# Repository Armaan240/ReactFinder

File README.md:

# ReactFinder

React Finder is Mememory Testing Game which works like , when you press the start button four led makes a Interesting Sequence and a order , the game is simple follow the exsact order of leds if you pressed correct button buzzer beeps and all are pressed correct Buzzer Beeps with A winning sound and New Level will start harder than the other , currently it have only 10 levels But All of them Are random so You can Still Enjoy if all of them is Played which difficult but Who knows , if only one sequence was pressed incorrectly buzzer beeps with a losing sound and thus you have to restart 

---
### Why i Made This?
i always Wnated to create A hardware based Game, so pathfinder hepled me and give me a motivation so that i could make a tick on my bucket list , also i thanks to meghana , she hepled me out in every doubt is asked i liked her patience and kindness which led to make React Finder 

### Some Key Features 

* 4 LEDs Turn on in a random Order 
* Press buttons to repeat the correct sequence with A buzzer beep
* Win = buzzer celebration sound + level up
* Lose = if you were un Successfull in Order ,buzzer fail tone + restart game

## Images 

.png)
.png)
.png)

### 🔩 Bill of Materials (BOM)

| Qty | Component         | Description                          | Example Part No / Notes   |
| --- | ----------------- | ------------------------------------ | ------------------------- |
| 1   | Seeed XIAO RP2040 | Microcontroller                      | Seeed Studio 102010428    |
| 4   | LEDs (any color)  | Visual feedback                      | 3mm or 5mm LEDs           |
| 4   | 220Ω Resistors    | For current-limiting LEDs            | One per LED               |
| 5   | Push Buttons      | Tactile switches for input           | Through-hole 6x6mm        |
| 1   | Buzzer (Active)   | Audio output                         | 5V Active Buzzer Module   |
| 1   | Breadboard        | For prototyping                      | Optional if not soldering |
| 10+ | Jumper Wires      | Connections                          | Male-to-male              |
| 4   | 3D Printed KeyCaps| Power and programming                | For XIAO RP2040           |

---

### 🛠️ Wiring Diagram 

| Function     | XIAO RP2040 Pin | Component |
| ------------ | --------------- | --------- |
| LED1         | GPIO26 (A0)     | D1        |
| LED2         | GPIO27 (A1)     | D2        |
| LED3         | GPIO28 (A2)     | D3        |
| LED4         | GPIO29 (A3)     | D4        |
| Button 1     | GPIO1 (RX)      | SW1       |
| Button 2     | GPIO0 (TX)      | SW2       |
| Button 3     | GPIO7 (SCL)     | SW3       |
| Button 4     | GPIO6 (SDA)     | SW4       |
| Start Button | GPIO5           | SW5       |
| Buzzer       | GPIO4           | BUZZ      |

---

### 📷 Optional Feature To add In future 

* Add a 0.96" OLED screen to display current level or high score
* 3D print a custom game
* Time-based challenge mode
* EEPROM save high score
* Multiplayer mode
* Web-based scoreboard (via Wi-Fi on ESP32 variant)

**For Pcb files and Models Please Check out OtherFiles Folder and PLease Ignore HopeFinder Name (it Was Choosen Fisrt But Didnt LIke it)**

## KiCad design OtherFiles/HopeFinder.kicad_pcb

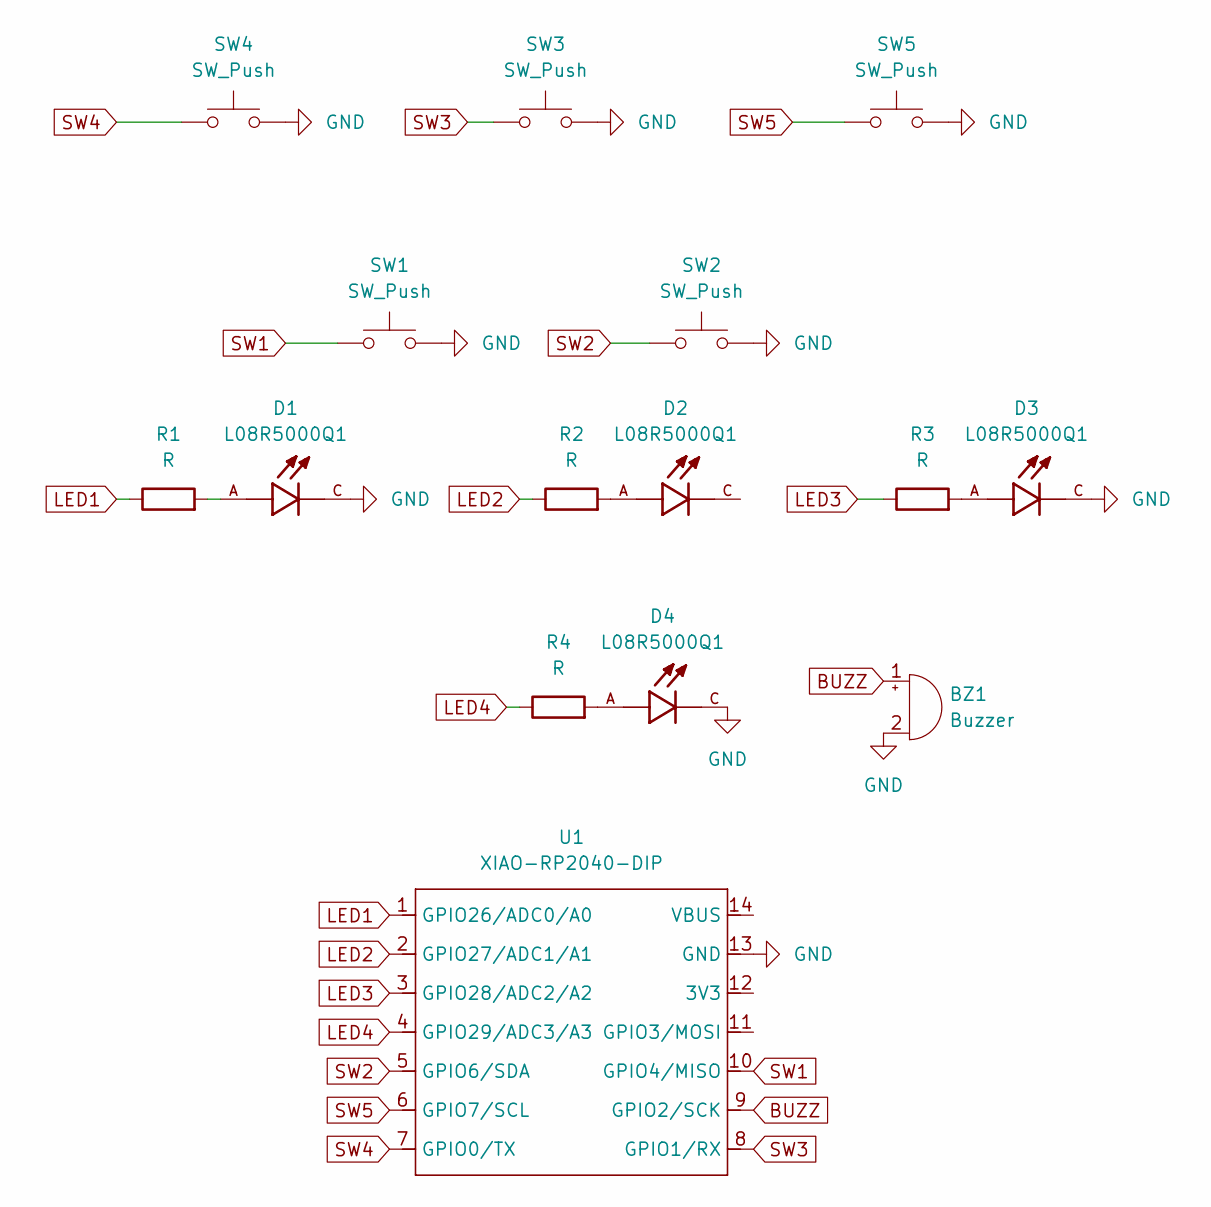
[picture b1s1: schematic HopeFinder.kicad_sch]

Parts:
BZ1: Buzzer; Buzzer_12x9.5RM7.6
D1, D2, D3, D4: L08R5000Q1; LEDRD254W57D500H1070; PARTREV NA
R1, R2, R3, R4: R; R_Axial_DIN0204_L3.6mm_D1.6mm_P5.08mm_Horizontal
SW1, SW2, SW3, SW4, SW5: SW_Push; SW_Cherry_MX_1.00u_PCB
U1: XIAO-RP2040-DIP

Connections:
BUZZ: BZ1.1 (+), U1.9 (GPIO2/SCK)
GND: BZ1.2 (-), D1.C, D3.C, D4.C, SW1.2, SW2.2, SW3.2, SW4.2, SW5.2, U1.13 (GND)
LED1: R1.1, U1.1 (GPIO26/ADC0/A0)
LED2: R2.1, U1.2 (GPIO27/ADC1/A1)
LED3: R3.1, U1.3 (GPIO28/ADC2/A2)
LED4: R4.1, U1.4 (GPIO29/ADC3/A3)
unnamed: D1.A, R1.2
unnamed: D2.A, R2.2
unnamed: D3.A, R3.2
unnamed: D4.A, R4.2
SW1: SW1.1, U1.10 (GPIO4/MISO)
SW2: SW2.1, U1.5 (GPIO6/SDA)
SW3: SW3.1, U1.8 (GPIO1/RX)
SW4: SW4.1, U1.7 (GPIO0/TX)
SW5: SW5.1, U1.6 (GPIO7/SCL)

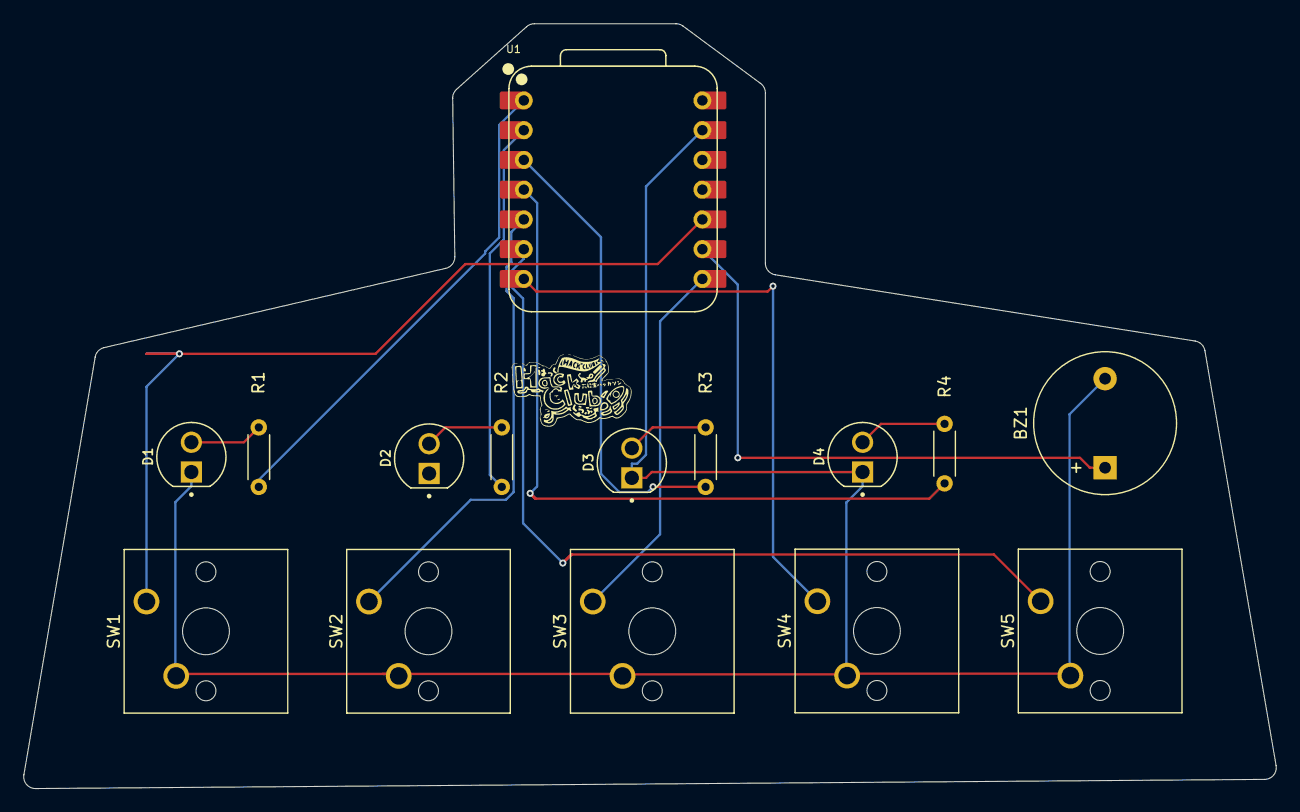
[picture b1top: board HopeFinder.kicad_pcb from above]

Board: 2 copper layers, 106.9 x 65.3 mm, 15 parts (0 on the bottom side), 15 nets.

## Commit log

2025-07-04 Create OtherFiles
2025-07-04 Update OtherFiles
2026-01-09 Fix image links in README.md
    Updated image links in the README file.
